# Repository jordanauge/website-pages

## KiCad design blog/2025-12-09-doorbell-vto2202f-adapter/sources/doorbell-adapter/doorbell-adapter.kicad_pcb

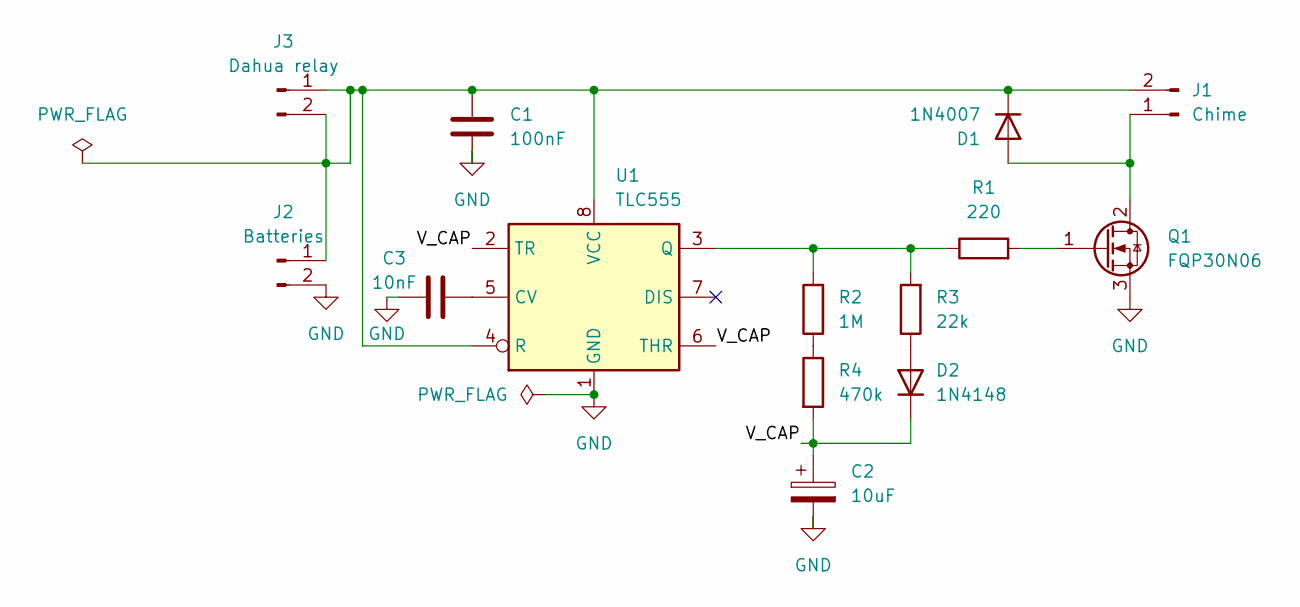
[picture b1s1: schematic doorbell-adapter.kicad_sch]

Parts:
C1: 100nF; C_Disc_D5.0mm_W2.5mm_P5.00mm
C2: 10uF; CP_Radial_D5.0mm_P2.00mm
C3: 10nF; C_Disc_D5.0mm_W2.5mm_P2.50mm
D1: 1N4007; D_DO-41_SOD81_P10.16mm_Horizontal
D2: 1N4148; D_DO-35_SOD27_P7.62mm_Horizontal
J1: Chime; TerminalBlock_Phoenix_PT-1,5-2-3.5-H_1x02_P3.50mm_Horizontal
J2: Batteries; TerminalBlock_Phoenix_PT-1,5-2-3.5-H_1x02_P3.50mm_Horizontal
J3: Dahua relay; TerminalBlock_Phoenix_PT-1,5-2-3.5-H_1x02_P3.50mm_Horizontal
Q1: FQP30N06; TO-220-3_Vertical
R1: 220; R_Axial_DIN0207_L6.3mm_D2.5mm_P10.16mm_Horizontal
R2: 1M; R_Axial_DIN0207_L6.3mm_D2.5mm_P10.16mm_Horizontal
R3: 22k; R_Axial_DIN0207_L6.3mm_D2.5mm_P10.16mm_Horizontal
R4: 470k; R_Axial_DIN0207_L6.3mm_D2.5mm_P10.16mm_Horizontal
U1: TLC555; DIP-8_W7.62mm

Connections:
/V_CAP: C2.1, D2.1 (K), R4.2, U1.2 (TR), U1.6 (THR)
GND: C1.2, C2.2, C3.1, J2.2, Q1.3 (S), U1.1 (GND)
unnamed: D1.2 (A), J1.1, Q1.2 (D)
unnamed: C1.1, D1.1 (K), J1.2, J2.1, J3.1, J3.2, U1.4 (R), U1.8 (VCC)
unnamed: D2.2 (A), R3.1
unnamed: Q1.1 (G), R1.2
unnamed: R2.1, R4.1
unnamed: C3.2, U1.5 (CV)
unnamed: R1.1, R2.2, R3.2, U1.3 (Q)

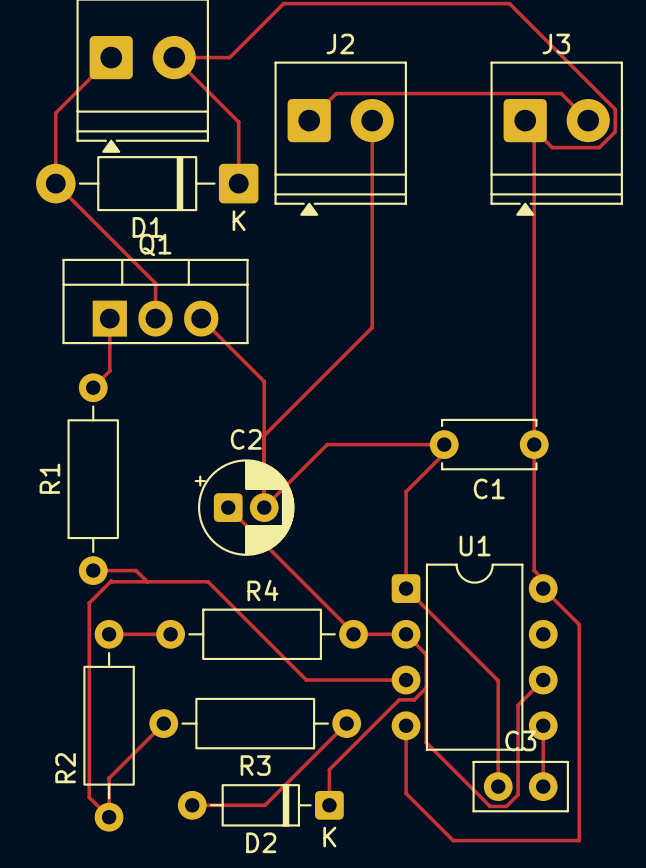
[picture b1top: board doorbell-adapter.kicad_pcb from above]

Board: 2 copper layers, 14 parts (0 on the bottom side), 9 nets.
